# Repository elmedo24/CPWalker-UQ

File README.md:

# CPWalker-UQ
En este repositorio se encuentran los archivos básicos para la contrucción de un prototipo de exoesqueleto basado en la plataforma CPWalker

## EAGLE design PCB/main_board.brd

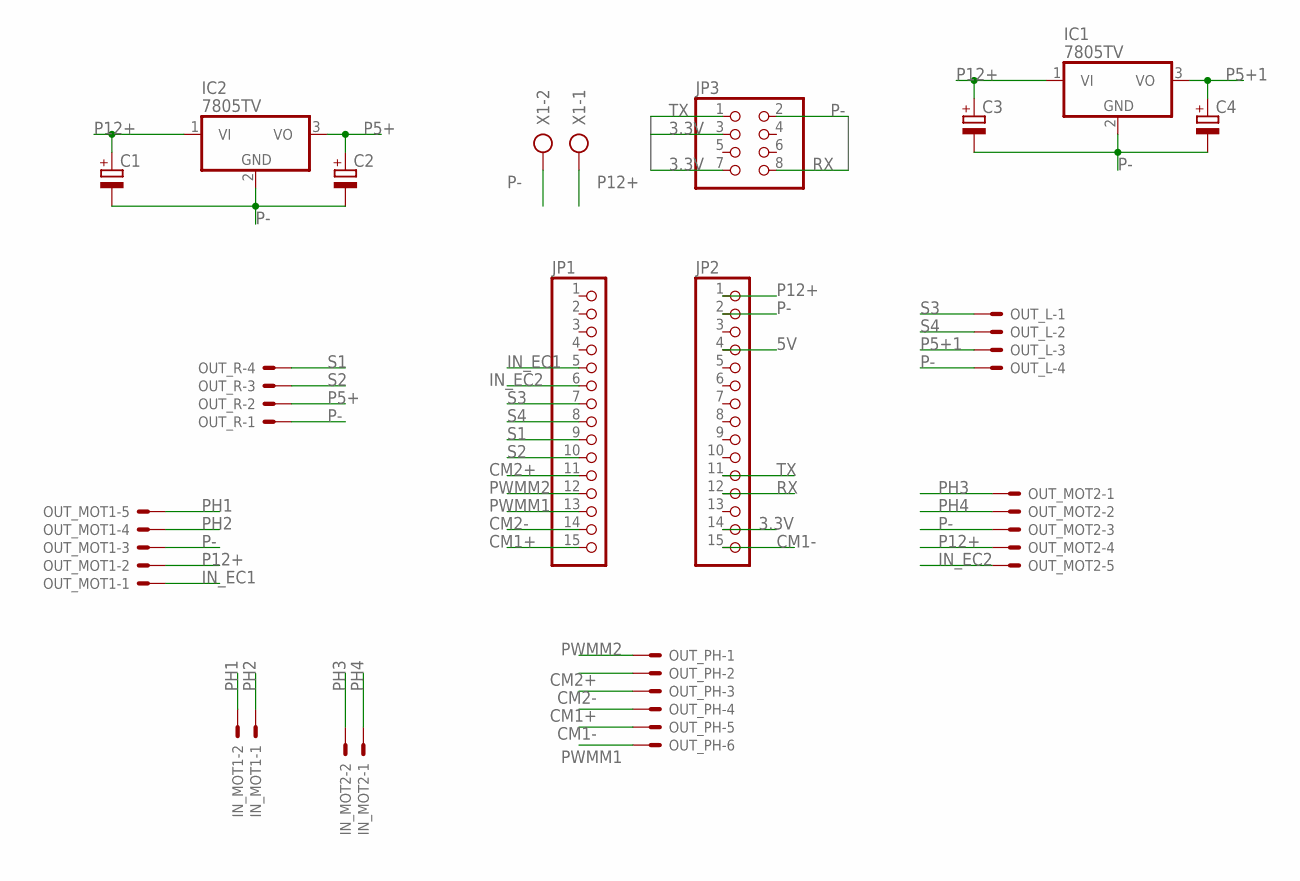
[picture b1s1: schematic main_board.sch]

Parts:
C1, C2, C3, C4: CPOL-EUE3.5-10; E3,5-10
IC1, IC2: 7805TV; TO220V
IN_MOT1, IN_MOT2: 22-23-2021
JP1, JP2: PINHD-1X15; 1X15
JP3: PINHD-2X4; 2X04
OUT_L: 22-23-2041
OUT_MOT1, OUT_MOT2: 22-23-2051
OUT_PH: 22-23-2061
OUT_R: 22-23-2041
X1: AK300/2

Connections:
3.3V: JP2.14, JP3.3, JP3.7
5V: JP2.4
CM1+: JP1.15, OUT_PH.4
CM1-: JP2.15, OUT_PH.5
CM2+: JP1.11, OUT_PH.2
CM2-: JP1.14, OUT_PH.3
IN_EC1: JP1.5, OUT_MOT1.1
IN_EC2: JP1.6, OUT_MOT2.5
P5+: C2.+, IC2.3 (VO), OUT_R.2
P5+1: C4.+, IC1.3 (VO), OUT_L.3
P12+: C1.+, C3.+, IC1.1 (VI), IC2.1 (VI), JP2.1, OUT_MOT1.2, OUT_MOT2.4, X1.1
P-: C1.-, C2.-, C3.-, C4.-, IC1.2 (GND), IC2.2 (GND), JP2.2, JP3.2, OUT_L.4, OUT_MOT1.3, OUT_MOT2.3, OUT_R.1, X1.2
PH1: IN_MOT1.2, OUT_MOT1.5
PH2: IN_MOT1.1, OUT_MOT1.4
PH3: IN_MOT2.2, OUT_MOT2.1
PH4: IN_MOT2.1, OUT_MOT2.2
PWMM1: JP1.13, OUT_PH.6
PWMM2: JP1.12, OUT_PH.1
RX: JP2.12, JP3.8
S1: JP1.9, OUT_R.4
S2: JP1.10, OUT_R.3
S3: JP1.7, OUT_L.1
S4: JP1.8, OUT_L.2
TX: JP2.11, JP3.1

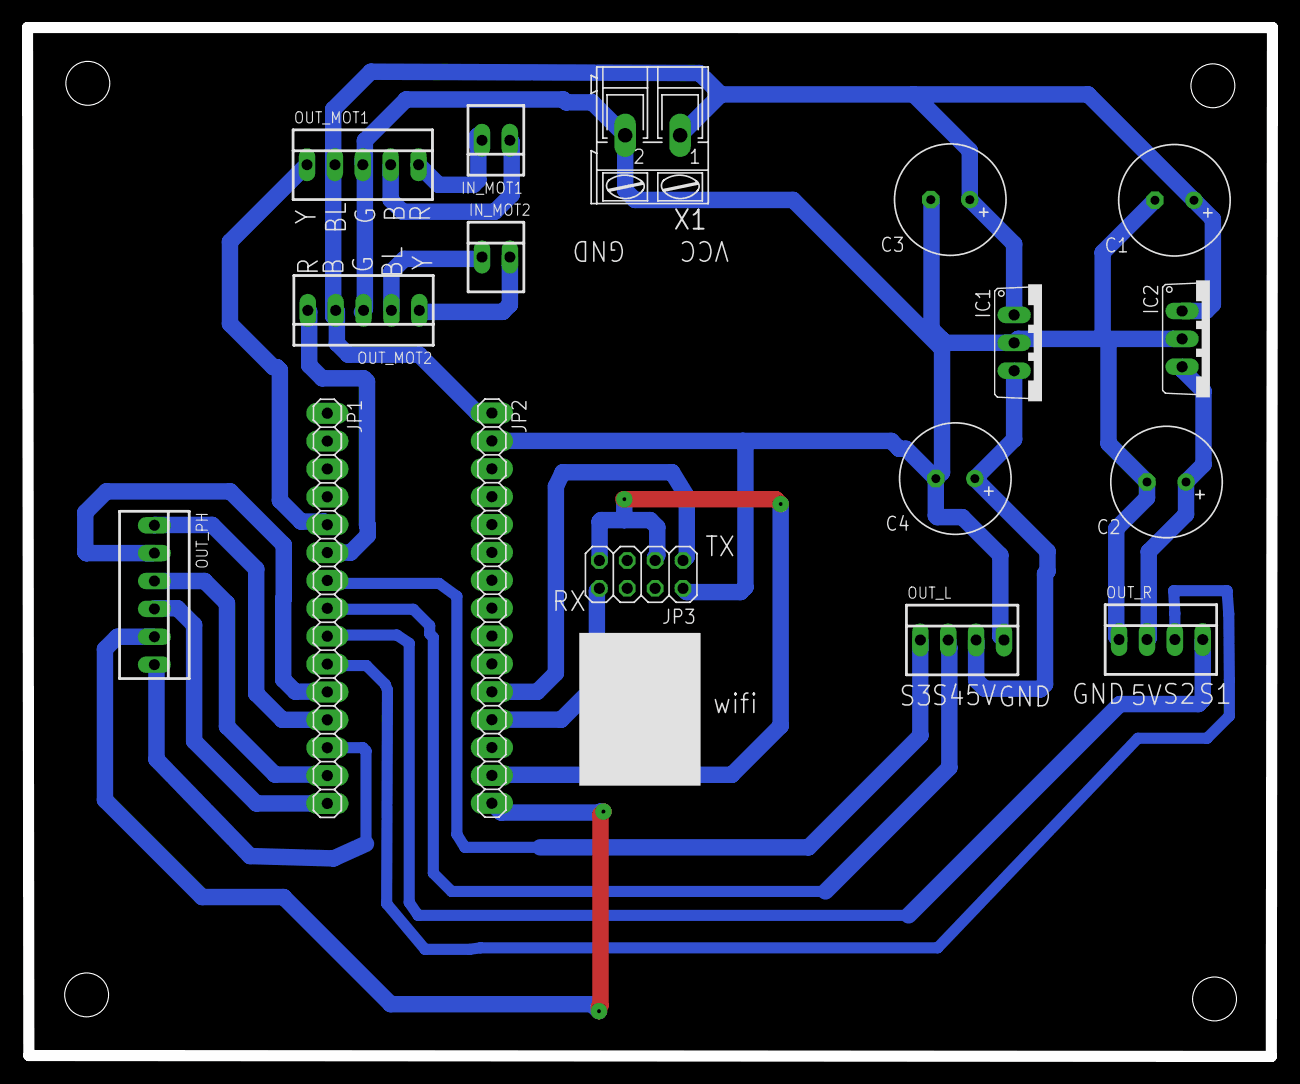
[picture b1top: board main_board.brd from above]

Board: 2 copper layers, 113.4 x 93.8 mm, 17 parts (0 on the bottom side), 23 nets.
